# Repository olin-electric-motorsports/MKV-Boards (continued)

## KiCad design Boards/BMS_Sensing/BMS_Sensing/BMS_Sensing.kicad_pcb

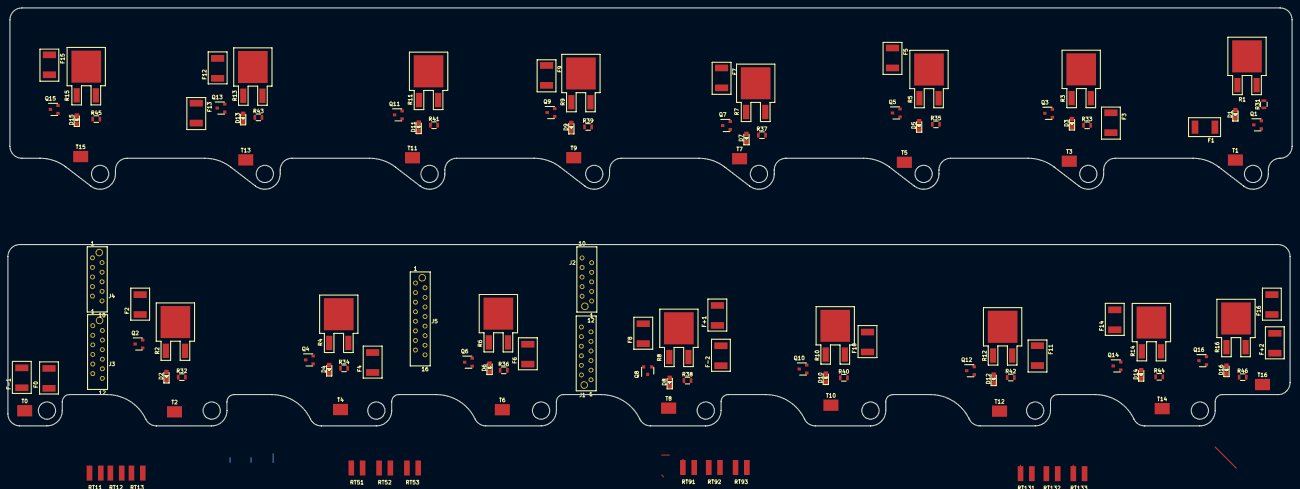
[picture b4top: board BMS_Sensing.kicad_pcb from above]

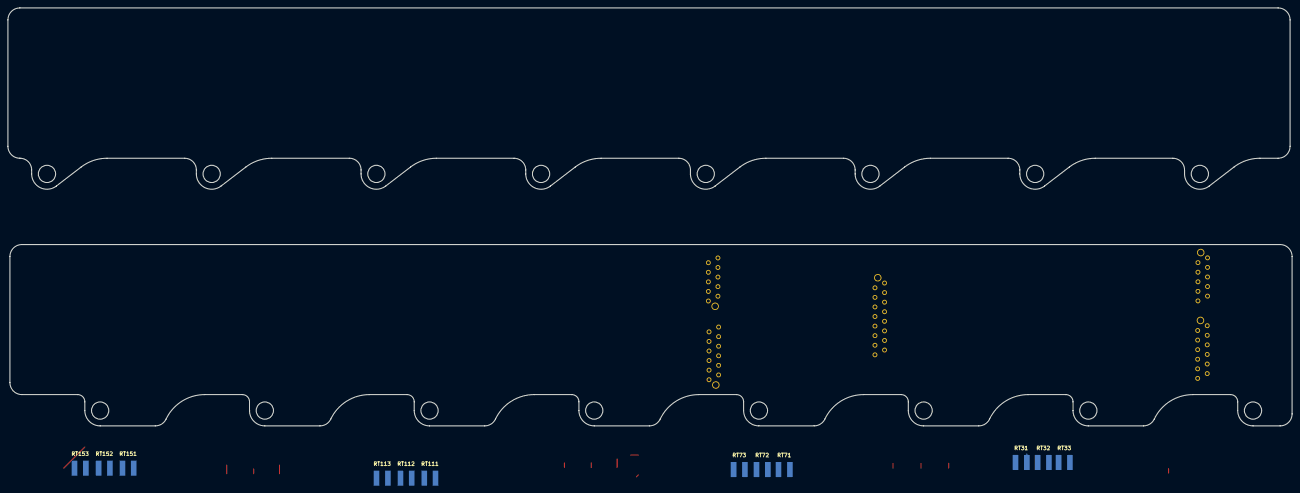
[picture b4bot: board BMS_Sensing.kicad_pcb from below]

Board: 2 copper layers, 340.6 x 110.9 mm, 131 parts (12 on the bottom side), 110 nets.

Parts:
D1, D2, D3, D4, D5, D6, D7, D8, D9, D10, D11, D12, D13, D14, D15, D16: LED_0805; LED_0805_OEM
F0, F1, F2, F3, F4, F5, F6, F7, F8, F9, F10, F11, F12, F13, F14, F15, F16: 200mA_Fuse; Fuse_1812
F+1, F+2: 200mA_Fuse; Fuse_1812
F-1, F-2: 200mA_Fuse; Fuse_1812
J1: MM_M_VT_10; micromatch_female_vert_12
J2, J4: MM_M_VT_12; micromatch_female_vert_10
J3: MM_M_VT_12; micromatch_female_vert_12
J5: MM_M_VT_16; micromatch_female_vert_16
Q1, Q2, Q3, Q4, Q5, Q6, Q7, Q8, Q9, Q10, Q11, Q12, Q13, Q14, Q15, Q16: BSS308PE; SOT-23-3_OEM
R1, R2, R3, R4, R5, R6, R7, R8, R9, R10, R11, R12, R13, R14, R15, R16: R_3.3_25W_TO163; PWR163
R31, R32, R33, R34, R35, R36, R37, R38, R39, R40, R41, R42, R43, R44, R45, R46: R_475; R_0805_OEM
RT11, RT12, RT13, RT31, RT32, RT33, RT51, RT52, RT53, RT71, RT72, RT73, RT91, RT92, RT93, RT111, RT112, RT113, RT131, RT132, RT133, RT151, RT152, RT153: Thermistor
T0, T1, T2, T3, T4, T5, T6, T7, T8, T9, T10, T11, T12, T13, T14, T15, T16: Tab_connect_BMS

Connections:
/C0: F0.2, J1.9
/C1: F1.2, J1.8
/C1_T1: J1.7, RT11.1
/C1_T2: J1.6, RT12.1
/C1_T3: J1.5, RT13.1
/C2: F2.2, J2.11
/C3: F3.2, J1.4
/C3_T1: J2.9, RT31.1
/C3_T2: J2.8, RT32.1
/C3_T3: J2.7, RT33.1
/C4: F4.2, J2.10
/C5: F5.2, J1.3
/C5_T1: J1.2, RT51.1
/C5_T2: J1.1, RT52.1
/C5_T3: J3.12, RT53.1
/C6: F6.2, J2.6
/C7: F7.2, J3.11
/C7_T1: J2.2, RT71.1
/C7_T2: J2.1, RT72.1
/C8: F8.2, J2.3
/C9: F9.2, J3.10
/C9_T1: J3.9, RT91.1
/C9_T2: J3.8, RT92.1
/C9_T3: J3.7, RT93.1
/C10: F10.2, J4.11
/C11: F11.2, J3.6
/C11_T1: J4.9, RT111.1
/C11_T2: J4.8, RT112.1
/C11_T3: J4.7, RT113.1
/C12: F12.2, J4.10
/C13: F13.2, J3.5
/C13_T1: J3.4, RT131.1
/C13_T2: J3.3, RT132.1
/C13_T3: J3.2, RT133.1
/C14: F14.2, J4.6
/C15: F15.2, J3.1
/C15_T1: J4.3, RT151.1
/C15_T2: J4.2, RT152.1
/C15_T3: J4.1, RT153.1
/C16: F16.2, J4.4
/GND1: RT11.2, RT12.2, RT13.2, RT31.2, RT32.2, RT33.2, RT51.2, RT52.2, RT53.2, RT71.2, RT72.2, RT73.2, RT91.2, RT92.2, RT93.2, RT111.2, RT112.2, RT113.2, RT131.2, RT132.2, RT133.2, RT151.2, RT152.2, RT153.2
/Q1: J5.16, Q1.1
/Q2: J5.15, Q2.1
/Q3: J5.14, Q3.1
/Q4: J5.13, Q4.1
/Q5: J5.12, Q5.1
/Q6: J5.11, Q6.1
/Q7: J5.10, Q7.1
/Q8: J5.9, Q8.1
/Q9: J5.8, Q9.1
/Q10: J5.7, Q10.1
/Q11: J5.6, Q11.1
/Q12: J5.5, Q12.1
/Q13: J5.4, Q13.1
/Q14: J5.3, Q14.1
/Q15: J5.2, Q15.1
/Q16: J5.1, Q16.1
/V+1: F+1.2, J4.5
/V+2: F+2.2, J2.5
/V-1: F-1.2, J2.4
/V-2: F-2.2, J1.10
unnamed: D1.1, R31.1
unnamed: D1.2, Q1.3, R1.1
unnamed: D2.1, R32.1
unnamed: D2.2, Q2.3, R2.1
unnamed: D3.1, R33.1
unnamed: D3.2, Q3.3, R3.1
unnamed: D4.1, R34.1
unnamed: D4.2, Q4.3, R4.1
unnamed: D5.1, R35.1
unnamed: D5.2, Q5.3, R5.1
unnamed: D6.1, R36.1
unnamed: D6.2, Q6.3, R6.1
unnamed: D7.1, R37.1
unnamed: D7.2, Q7.3, R7.1
unnamed: D8.1, R38.1
unnamed: D8.2, Q8.3, R8.1
unnamed: D9.1, R39.1
unnamed: D9.2, Q9.3, R9.1
unnamed: D10.1, R40.1
unnamed: D10.2, Q10.3, R10.1
unnamed: D11.1, R41.1
unnamed: D11.2, Q11.3, R11.1
unnamed: D12.1, R42.1
unnamed: D12.2, Q12.3, R12.1
unnamed: D13.1, R43.1
unnamed: D13.2, Q13.3, R13.1
unnamed: D14.1, R44.1
unnamed: D14.2, Q14.3, R14.1
unnamed: D15.1, R45.1
unnamed: D15.2, Q15.3, R15.1
unnamed: D16.1, R46.1
unnamed: D16.2, Q16.3, R16.1
unnamed: F1.1, Q1.2, R2.2, R32.2
unnamed: F2.1, Q2.2, R3.2, R33.2
unnamed: F3.1, Q3.2, R4.2, R34.2
unnamed: F4.1, Q4.2, R5.2, R35.2
unnamed: F5.1, Q5.2, R6.2, R36.2
unnamed: F6.1, Q6.2, R7.2, R37.2
unnamed: F7.1, Q7.2, R8.2, R38.2
unnamed: F9.1, Q9.2, R10.2, R40.2
unnamed: F10.1, Q10.2, R11.2, R41.2
unnamed: F11.1, Q11.2, R12.2, R42.2
unnamed: F12.1, Q12.2, R13.2, R43.2
unnamed: F13.1, Q13.2, R14.2, R44.2
unnamed: F14.1, Q14.2, R15.2, R45.2
unnamed: F15.1, Q15.2, R16.2, R46.2
unnamed: F8.1, F+1.1, F-2.1, Q8.2, R9.2, R39.2
unnamed: F16.1, F+2.1, Q16.2
unnamed: F0.1, F-1.1, R1.2, R31.2

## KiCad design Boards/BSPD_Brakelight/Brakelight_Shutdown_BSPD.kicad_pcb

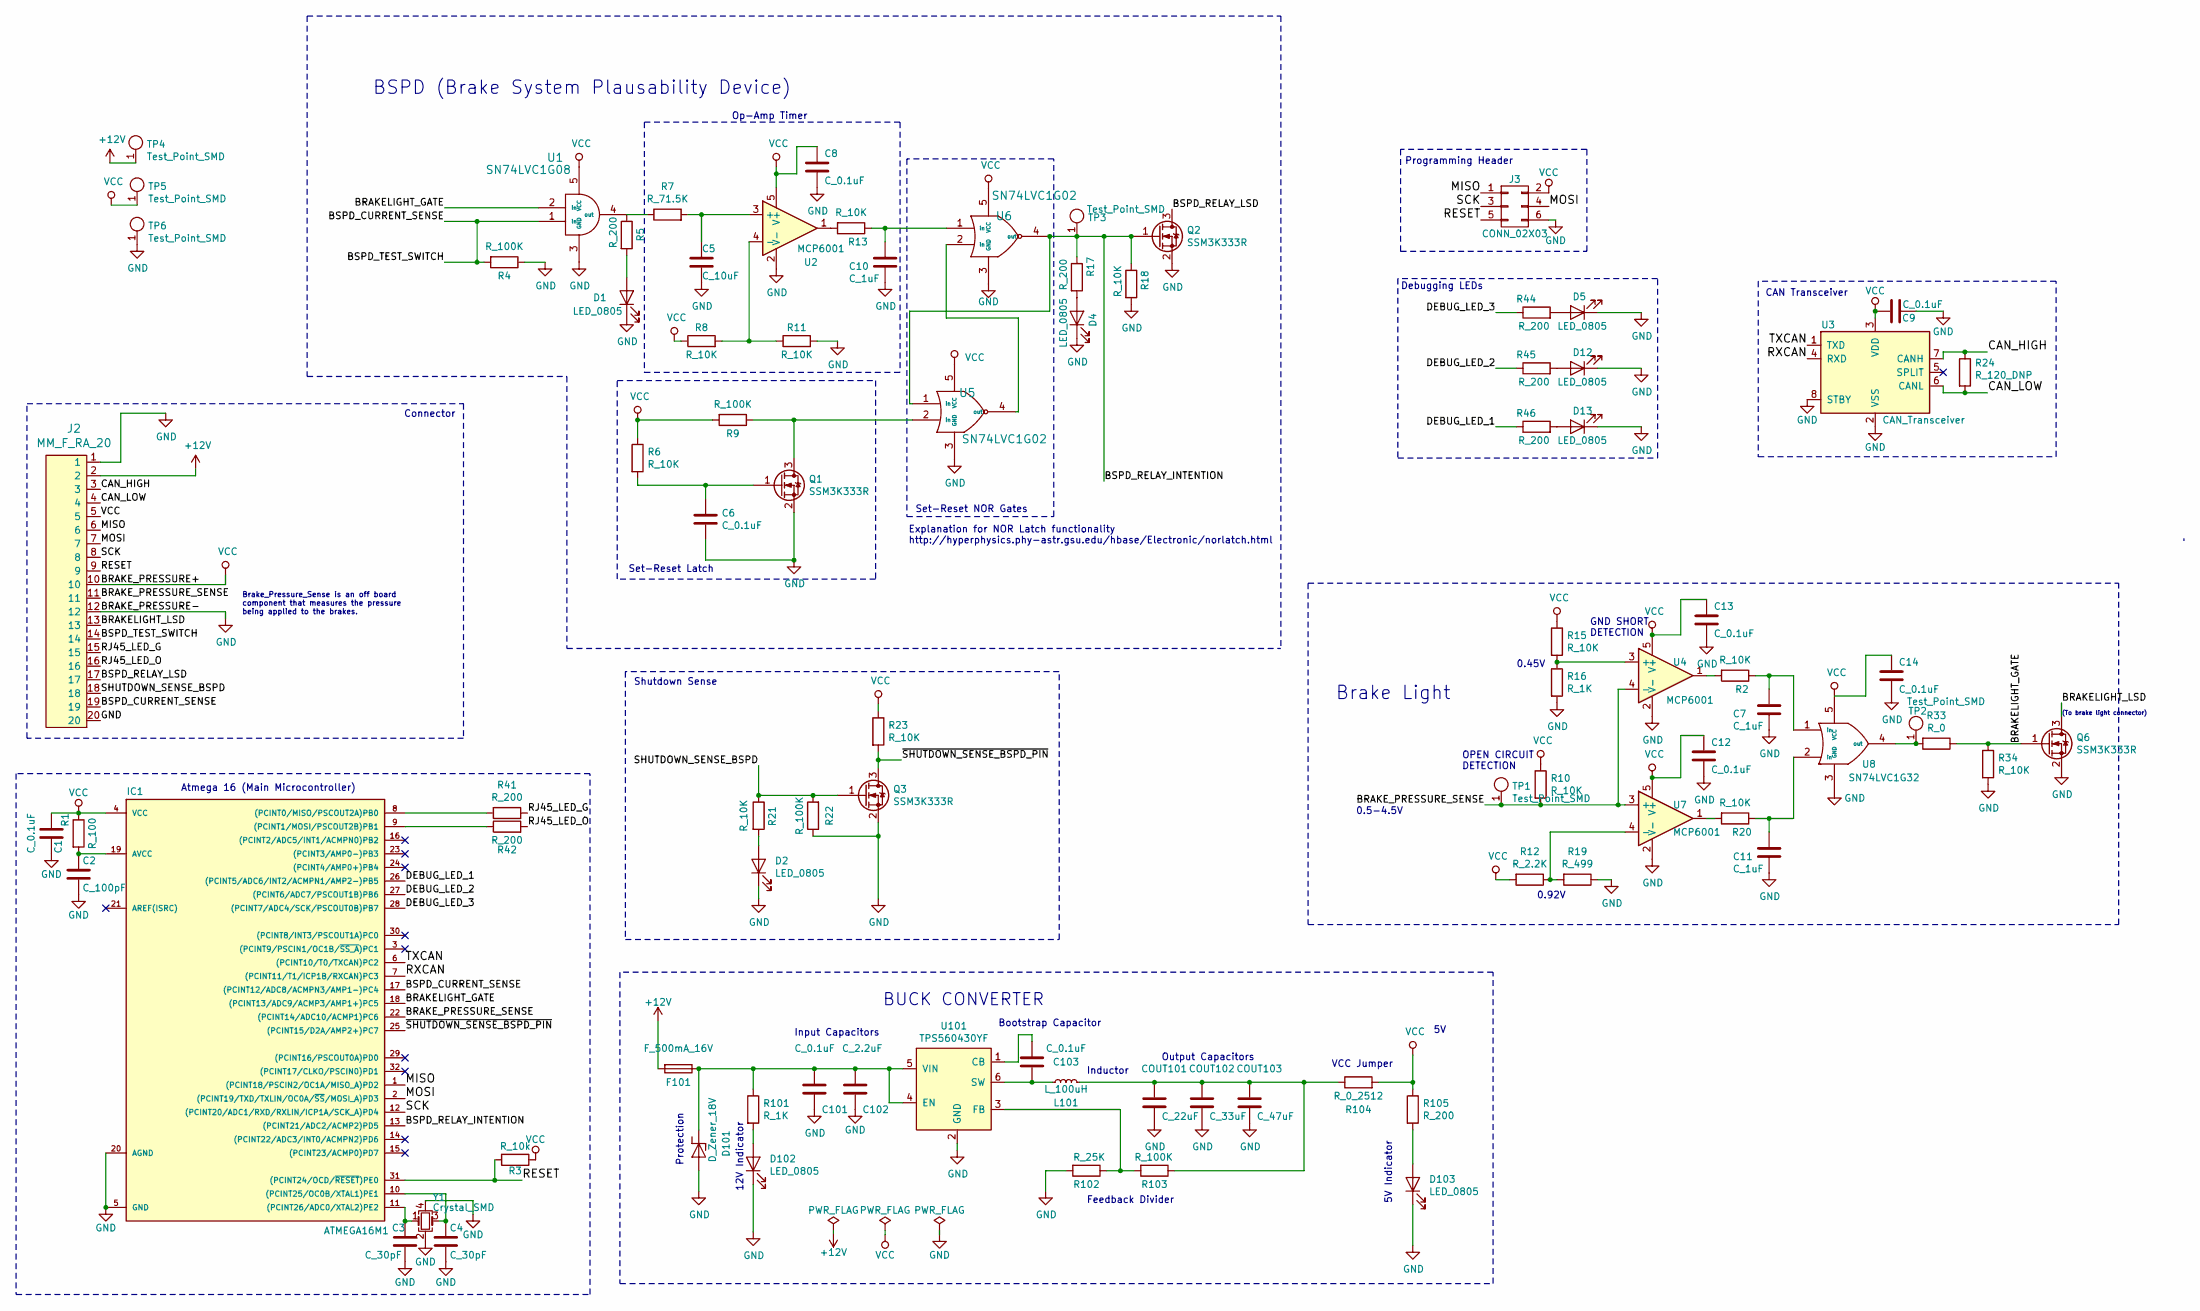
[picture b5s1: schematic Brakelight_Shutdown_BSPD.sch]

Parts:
C1, C6, C8, C9, C12, C13, C14, C101, C103: C_0.1uF; C_0805_OEM; MPN 478-3352-1-ND
C2: C_100pF; C_0805_OEM; MPN 732-7852-1-ND
C3, C4: C_30pF; C_0805_OEM; MPN 1276-1130-1-ND
C5: C_10uF; C_0805_OEM; MPN 1276-1052-1-ND
C7, C10, C11: C_1uF; C_0805_OEM; MPN 1276-2887-1-ND
C102: C_2.2uF; C_0603_1608Metric; MPN 311-1451-1-ND
COUT101: C_22uF; C_1206_OEM; MPN 445-11693-1-ND
COUT102: C_33uF; Fuse_1812; MPN 445-3924-1-ND
COUT103: C_47uF; C_0805_OEM; MPN 1276-6467-1-ND
D1, D2, D4, D5, D12, D13, D102, D103: LED_0805; LED_0805_OEM; MPN 475-1410-1-ND
D101: D_Zener_18V; DO-214AA; MPN SMBJ5355B-TPMSCT-ND
F101: F_500mA_16V; Fuse_1210; MPN 507-1786-1-ND
IC1: ATMEGA16M1; TQFP-32_7x7mm_Pitch0.8mm; MPN ATMEGA16M1-AU-ND
J2: MM_F_RA_20; micromatch_female_ra_20; MPN 2-338070-0
J3: CONN_02X03; Pin_Header_Straight_2x03; MPN 609-3234-ND
L101: L_100uH; L_100uH_OEM; MPN 445-15759-1-ND
Q1, Q2, Q3, Q6: SSM3K333R; SOT-23F; MPN SSM3K333RLFCT-ND
R1: R_100; R_0805_OEM; MPN RNCP0805FTD100RCT-ND
R2, R6, R8, R10, R11, R13, R15, R18, R20, R21, R23, R34: R_10K; R_0805_OEM; MPN CRS0805-FX-1002ELFCT-ND
R3: R_10k; R_0805_OEM; MPN CRS0805-FX-1002ELFCT-ND
R4, R9, R22, R103: R_100K; R_0805_OEM; MPN P100KCCT-ND
R5, R17, R41, R42, R44, R45, R46, R105: R_200; R_0805_OEM; MPN RMCF0805JT200RCT-ND
R7: R_71.5K; R_0805_OEM; MPN P1.07KDACT-ND
R12: R_2.2K; R_0805_OEM; MPN RMCF0805FT2K20CT-ND
R16, R101: R_1K; R_0805_OEM; MPN RNCP0805FTD1K00CT-ND
R19: R_499; R_0805_OEM; MPN P499CCT-ND
R24: R_120_DNP; R_0805_OEM; MPN 667-ERJ-6ENF1200V
R33: R_0; R_0603_1608Metric; MPN P0.0GCT-ND
R102: R_25K; R_0805_OEM; MPN A124124CT-ND; Digi-key Part Number CPF-A-0805B25KE
R104: R_0_2512; R_2512_OEM; MPN A121322CT-ND
TP1, TP2, TP3, TP4, TP5, TP6: Test_Point_SMD
U1: SN74LVC1G08; SOT-23-5_OEM; MPN 296-11601-2-ND
U2, U4, U7: MCP6001; SOT-23-5; MPN MCP6001T-I/OTCT-ND
U3: CAN_Transceiver; SOIC-8_3.9x4.9mm_Pitch1.27mm_OEM; MPN MCP2561-E/SN-ND
U5, U6: SN74LVC1G02; SOT-23-5_OEM; MPN 296-11597-1-ND
U8: SN74LVC1G32; SOT-23-5_OEM; MPN 296-9847-1-ND
U101: TPS560430YF; SOT-23-6_OEM; MPN TPS560430YFDBVR-ND
Y1: Crystal_SMD; Crystal_SMD_FA238; MPN 887-1125-1-ND

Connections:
+12V: F101.2, J2.2, TP4.1
/BRAKELIGHT_GATE: IC1.18 ((PCINT13/ADC9/ACMP3/AMP1+)PC5), Q6.1 (G), R33.1, R34.1, U1.2 (in)
/BRAKELIGHT_LSD: J2.13, Q6.3 (D)
/BRAKE_PRESSURE_SENSE: IC1.22 ((PCINT14/ADC10/ACMP1)PC6), J2.11, R10.2, TP1.1, U4.4 (-), U7.3 (+)
/BSPD_CURRENT_SENSE: IC1.17 ((PCINT12/ADC8/ACMPN3/AMP1-)PC4), J2.14, J2.19, R4.2, U1.1 (in)
/BSPD_RELAY_INTENTION: IC1.13 ((PCINT21/ADC2/ACMP2)PD5), Q2.1 (G), R17.1, R18.1, TP3.1, U5.1 (in), U6.4 (out)
/BSPD_RELAY_LSD: J2.17, Q2.3 (D)
/CAN_HIGH: J2.3, R24.1, U3.7 (CANH)
/CAN_LOW: J2.4, R24.2, U3.6 (CANL)
/DEBUG_LED_1: IC1.26 ((PCINT5/ADC6/INT2/ACMPN1/AMP2-)PB5), R46.1
/DEBUG_LED_2: IC1.27 ((PCINT6/ADC7/PSCOUT1B)PB6), R45.1
/DEBUG_LED_3: IC1.28 ((PCINT7/ADC4/SCK/PSCOUT0B)PB7), R44.1
/MISO: IC1.1 ((PCINT18/PSCIN2/OC1A/MISO_A)PD2), J2.6, J3.1
/MOSI: IC1.2 ((PCINT19/TXD/TXLIN/OC0A/~SS~/MOSI_A)PD3), J2.7, J3.4
/RESET: IC1.31 ((PCINT24/OCD/~RESET~)PE0), J2.9, J3.5, R3.2
/RJ45_LED_G: J2.15, R41.1
/RJ45_LED_O: J2.16, R42.2
/RXCAN: IC1.7 ((PCINT11/T1/ICP1B/RXCAN)PC3), U3.4 (RXD)
/SCK: IC1.12 ((PCINT20/ADC1/RXD/RXLIN/ICP1A/SCK_A)PD4), J2.8, J3.3
/SHUTDOWN_SENSE_BSPD: J2.18, Q3.1 (G), R21.1, R22.2
/TXCAN: IC1.6 ((PCINT10/T0/TXCAN)PC2), U3.1 (TXD)
/~SHUTDOWN_SENSE_BSPD_PIN: IC1.25 ((PCINT15/D2A/AMP2+)PC7), Q3.3 (D), R23.2
GND: C1.2, C2.2, C3.2, C4.2, C5.2, C6.2, C7.2, C8.2, C9.2, C10.2, C11.2, C12.2, C13.2, C14.2, C101.2, C102.2, COUT101.2, COUT102.2, COUT103.2, D1.1 (K), D2.1 (K), D4.1 (K), D5.1 (K), D12.1 (K), D13.1 (K), D101.2 (A), D102.1 (K), D103.1 (K), IC1.5 (GND), IC1.20 (AGND), J2.1, J2.12, J2.20, J3.6, Q1.2 (S), Q2.2 (S), Q3.2 (S), Q6.2 (S), R4.1, R11.2, R16.2, R18.2, R19.1, R22.1, R34.2, R102.2, TP6.1, U1.3 (GND), U2.2 (V-), U3.2 (VSS), U3.8 (STBY), U4.2 (V-), U5.3 (GND), U6.3 (GND), U7.2 (V-), U8.3 (GND), U101.2 (GND), Y1.2, Y1.4
unnamed: C2.1, IC1.19 (AVCC), R1.2
unnamed: C3.1, IC1.11 ((PCINT26/ADC0/XTAL2)PE2), Y1.1
unnamed: C4.1, IC1.10 ((PCINT25/OC0B/XTAL1)PE1), Y1.3
unnamed: C5.1, R7.2, U2.3 (+)
unnamed: C6.1, Q1.1 (G), R6.2
unnamed: C7.1, R2.1, U8.1 (in)
unnamed: C10.1, R13.1, U6.1 (in)
unnamed: C11.1, R20.1, U8.2 (in)
unnamed: C101.1, C102.1, D101.1 (K), F101.1, R101.1, U101.4 (EN), U101.5 (VIN)
unnamed: C103.1, L101.1, U101.6 (SW)
unnamed: C103.2, U101.1 (CB)
unnamed: COUT101.1, COUT102.1, COUT103.1, L101.2, R103.1, R104.1
unnamed: D1.2 (A), R5.2
unnamed: D2.2 (A), R21.2
unnamed: D4.2 (A), R17.2
unnamed: D5.2 (A), R44.2
unnamed: D12.2 (A), R45.2
unnamed: D13.2 (A), R46.2
unnamed: D102.2 (A), R101.2
unnamed: D103.2 (A), R105.2
unnamed: IC1.8 ((PCINT0/MISO/PSCOUT2A)PB0), R41.2
unnamed: IC1.9 ((PCINT1/MOSI/PSCOUT2B)PB1), R42.1
unnamed: Q1.3 (D), R9.1, U5.2 (in)
unnamed: R2.2, U4.1
unnamed: R5.1, R7.1, U1.4 (out)
unnamed: R8.2, R11.1, U2.4 (-)
unnamed: R12.1, R19.2, U7.4 (-)
unnamed: R13.2, U2.1
unnamed: R15.2, R16.1, U4.3 (+)
unnamed: R20.2, U7.1
unnamed: R33.2, TP2.1, U8.4 (out)
unnamed: R102.1, R103.2, U101.3 (FB)
unnamed: U5.4 (out), U6.2 (in)
VCC: C1.1, C8.1, C9.1, C12.1, C13.1, C14.1, IC1.4 (VCC), J2.5, J2.10, J3.2, R1.1, R3.1, R6.1, R8.1, R9.2, R10.1, R12.2, R15.1, R23.1, R104.2, R105.1, TP5.1, U1.5 (VCC), U2.5 (V+), U3.3 (VDD), U4.5 (V+), U5.5 (VCC), U6.5 (VCC), U7.5 (V+), U8.5 (VCC)

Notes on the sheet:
(To brake light connector)
Atmega 16 (Main Microcontroller)
BSPD (Brake System Plausability Device)
Op-Amp Timer
Set-Reset Latch
Set-Reset NOR Gates
Brake Light
Explanation for NOR Latch functionality http://hyperphysics.phy-astr.gsu.edu/hbase/Electronic/norlatch.html
Input Capacitors
12V Indicator
Protection
BUCK CONVERTER
Feedback Divider
Inductor
Bootstrap Capacitor
Output Capacitors
VCC Jumper
5V Indicator
0.92V
0.45V
0.5-4.5V
OPEN CIRCUIT DETECTION
GND SHORT DETECTION
Brake_Pressure_Sense is an off board component that measures the pressure being applied to the brakes.
CAN Transceiver
Programming Header
Debugging LEDs
Connector
Shutdown Sense

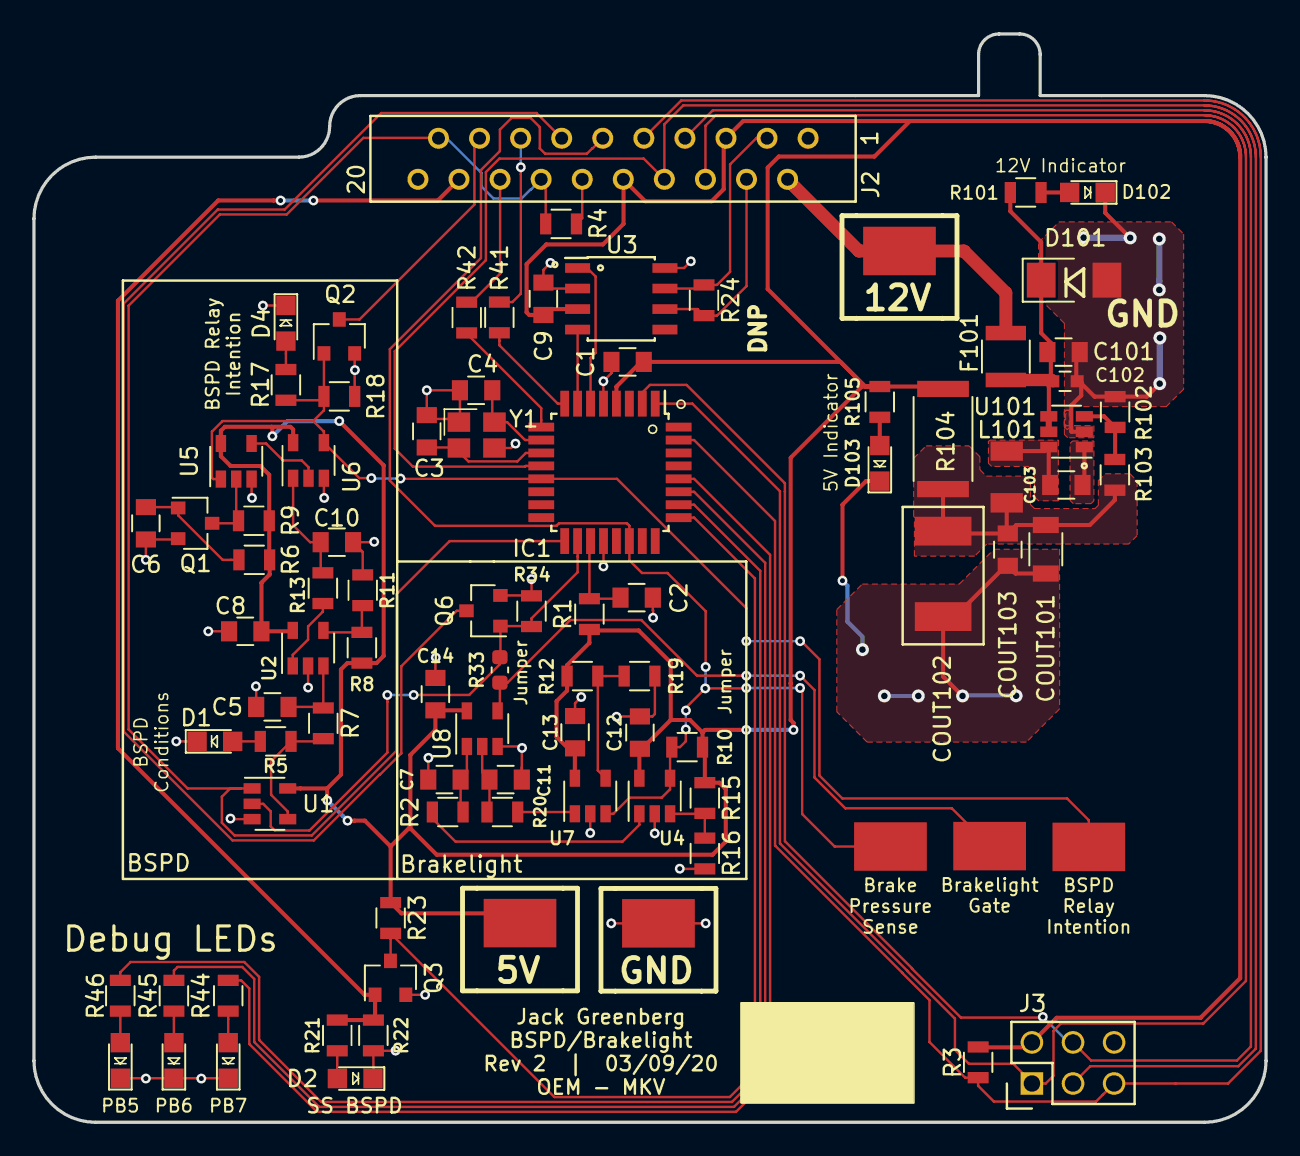
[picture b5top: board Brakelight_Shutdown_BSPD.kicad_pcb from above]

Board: 2 copper layers, 76.2 x 67.3 mm, 89 parts (0 on the bottom side), 57 nets.

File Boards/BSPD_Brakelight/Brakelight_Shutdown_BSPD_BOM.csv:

Reference, Quantity, Value, Footprint, Datasheet, MFN, MPN, Package, PurchasingLink, Digi-key Part Number, Link, Purchasing Link
C10 C7 C11 ,3,"C_1uF","footprints:C_0805_OEM","http://www.samsungsem.com/kr/support/product-search/mlcc/__i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","DK","1276-2887-1-ND","","https://www.digikey.com/product-detail/en/samsung-electro-me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","","",""
C102 ,1,"C_2.2uF","Capacitors_SMD:C_0603","http://www.yageo.com/documents/recent/UPY-GPHC_X5R_4V-to-50V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","DK","311-1451-1-ND","","https://www.digikey.com/product-detail/en/yageo/CC0603KRX5R6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","","",""
C2 ,1,"C_100pF","footprints:C_0805_OEM","https://content.kemet.com/datasheets/KEM_C1003_C0G_SMD.pdf","Digi-Key","399-1122-1-ND","Value","https://www.digikey.com/product-detail/en/kemet/C0805C101J5G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","","",""
C4 C3 ,2,"C_30pF","footprints:C_0805_OEM","https://media.digikey.com/pdf/Data%20Sheets/Samsung%20PDFs/C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","Digi-Key","1276-1130-1-ND","Value","https://www.digikey.com/product-detail/en/samsung-electro-me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","","",""
C5 ,1,"C_10uF","footprints:C_0805_OEM","http://www.samsungsem.com/kr/support/product-search/mlcc/__i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","DK","1276-1052-1-ND","","https://www.digikey.com/product-detail/en/samsung-electro-me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","","",""
C9 C8 C6 C1 C101 C103 C13 C12 C14 ,9,"C_0.1uF","footprints:C_0805_OEM","http://datasheets.avx.com/X7RDielectric.pdf","Digi-Key","478-3352-1-ND","Value","https://www.digikey.com/products/en?keywords=478-3352-1-ND","","",""
COUT101 ,1,"C_22uF","footprints:C_1206_OEM","https://product.tdk.com/info/en/catalog/datasheets/mlcc_comm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","DK","445-11693-1-ND","","https://www.digikey.com/product-detail/en/tdk-corporation/C3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","","",""
COUT102 ,1,"C_33uF","footprints:Fuse_1812","https://product.tdk.com/info/en/catalog/datasheets/mlcc_comm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","C4532X7R1C336M250KC","445-3924-1-ND","","https://www.digikey.com/product-detail/en/tdk-corporation/C4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","","",""
COUT103 ,1,"C_47uF","footprints:C_0805_OEM","http://www.samsungsem.com/kr/support/product-search/mlcc/__i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","DK","1276-6467-1-ND","","https://www.digikey.com/product-detail/en/samsung-electro-me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","","",""
D1 D4 D5 D12 D13 D103 D102 D2 ,8,"LED_0805","footprints:LED_0805_OEM","http://www.osram-os.com/Graphics/XPic9/00078860_0.pdf","DK","475-1410-1-ND","","https://www.digikey.com/products/en?keywords=475-1410-1-ND","","",""
D101 ,1,"D_Zener_18V","footprints:DO-214AA","http://www.mccsemi.com/up_pdf/SMBJ5338B-SMBJ5388B(SMB).pdf","DK","SMBJ5355B-TPMSCT-ND","","https://www.digikey.com/products/en?keywords=SMBJ5355B-TPMSCT-ND","","",""
F101 ,1,"F_500mA_16V","footprints:Fuse_1210","https://belfuse.com/resources/CircuitProtection/datasheets/0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","DK","507-1786-1-ND","","https://www.digikey.com/product-detail/en/bel-fuse-inc/0ZCH0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","","",""
IC1 ,1,"ATMEGA16M1","footprints:TQFP-32_7x7mm_Pitch0.8mm","http://www.atmel.com/Images/Atmel-8209-8-bit%20AVR%20ATmega1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","Digi-Key","ATMEGA16M1-AU-ND","Value","https://www.digikey.com/product-detail/en/atmel/ATMEGA16M1-A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","","",""
J2 ,1,"MM_F_RA_20","footprints:micromatch_female_ra_20","http://www.te.com/commerce/DocumentDelivery/DDEController?Ac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","TE","2-338070-0","","http://www.te.com/usa-en/product-2-338070-0.html","","",""
J3 ,1,"CONN_02X03","footprints:Pin_Header_Straight_2x03","http://portal.fciconnect.com/Comergent//fci/drawing/67996.pdf","Digi-Key","609-3234-ND","Value","https://www.digikey.com/product-detail/en/amphenol-fci/67997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","","",""
L101 ,1,"L_100uH","footprints:L_100uH","https://product.tdk.com/info/en/catalog/datasheets/inductor_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","Digikey","445-15759-1-ND","","","","https://www.digikey.com/product-detail/en/tdk-corporation/NL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",""
Q1 Q2 Q6 Q3 ,4,"SSM3K333R","footprints:SOT-23F","https://drive.google.com/drive/folders/0B-V-iZf33Y4GNzhDQTJZanJRbVk","DK","SSM3K333RLFCT-ND","","https://www.digikey.com/product-detail/en/toshiba-semiconduc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","","",""
R1 ,1,"R_100","footprints:R_0805_OEM","https://www.seielect.com/Catalog/SEI-rncp.pdf","Digi-Key","RNCP0805FTD100RCT-ND","Value","https://www.digikey.com/products/en?keywords=RNCP0805FTD100RCT-ND","","",""
R102 ,1,"R_25K","footprints:R_0805_OEM","https://www.te.com/commerce/DocumentDelivery/DDEController?A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","A124124CT-ND","","","https://www.digikey.com/product-detail/en/te-connectivity-pa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","CPF-A-0805B25KE","",""
R104 ,1,"R_0_2512","footprints:R_2512_OEM","http://www.te.com/commerce/DocumentDelivery/DDEController?Ac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","DK","A121322CT-ND","","https://www.digikey.com/products/en?keywords=A121322CT-ND","","",""
R12 ,1,"R_2.2K","footprints:R_0805_OEM","https://www.seielect.com/Catalog/SEI-RMCF_RMCP.pdf","DK","RMCF0805FT2K20CT-ND","","https://www.digikey.com/product-detail/en/stackpole-electron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","","",""
R14 R33 ,2,"R_0","footprints:R_0603_1608Metric","http://industrial.panasonic.com/www-cgi/jvcr13pz.cgi?E+PZ+3+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","DK","P0.0GCT-ND","","https://www.digikey.com/product-detail/en/panasonic-electron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","","",""
R16 R101 ,2,"R_1K","footprints:R_0805_OEM","https://www.seielect.com/Catalog/SEI-rncp.pdf","DK","RNCP0805FTD1K00CT-ND","","https://www.digikey.com/products/en?keywords=RNCP0805FTD1K00CT-ND","","",""
R19 ,1,"R_499","footprints:R_0805_OEM","https://industrial.panasonic.com/cdbs/www-data/pdf/RDA0000/A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","DK","P499CCT-ND","","https://www.digikey.com/product-detail/en/panasonic-electron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","","",""
R24 ,1,"R_120_DNP","footprints:R_0805_OEM","https://www.mouser.com/datasheet/2/315/AOA0000C304-1149620.pdf","DK","667-ERJ-6ENF1200V","","https://www.mouser.com/ProductDetail/Panasonic-Industrial-De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","","",""
R3 ,1,"R_10k","footprints:R_0805_OEM","http://www.bourns.com/data/global/pdfs/CRS.pdf","Digi-Key","CRS0805-FX-1002ELFCT-ND","Value","https://www.digikey.com/products/en?keywords=CRS0805-FX-1002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","","",""
R4 R9 R103 R22 ,4,"R_100K","footprints:R_0805_OEM","https://industrial.panasonic.com/cdbs/www-data/pdf/RDA0000/A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","DK","P100KCCT-ND","","https://www.digikey.com/product-detail/en/panasonic-electron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","","",""
R5 R17 R41 R42 R44 R45 R46 R105 ,8,"R_200","footprints:R_0805_OEM","https://www.seielect.com/Catalog/SEI-RMCF_RMCP.pdf","DK","RMCF0805JT200RCT-ND","","https://www.digikey.com/products/en?keywords=RMCF0805JT200RCT-ND","","",""
R7 ,1,"R_71.5K","footprints:R_0805_OEM","","DK","P1.07KDACT-ND","","","","",""
R8 R11 R13 R6 R18 R34 R15 R10 R2 R20 R23 R21 ,12,"R_10K","footprints:R_0805_OEM","http://www.bourns.com/data/global/pdfs/CRS.pdf","DK","CRS0805-FX-1002ELFCT-ND","","https://www.digikey.com/products/en?keywords=CRS0805-FX-1002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","","",""
U1 ,1,"SN74LVC1G08","footprints:SOT-23-5_OEM","http://www.ti.com/lit/ds/symlink/sn74lvc1g08.pdf","DK","296-11602-1-ND","","https://www.digikey.com/product-detail/en/texas-instruments/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","","",""
U101 ,1,"TPS560430YF","footprints:SOT-23-6_OEM","http://www.ti.com/lit/ds/symlink/tps560430.pdf","TPS560430YFDBVR-ND","TPS560430YFDBVR","","","","","https://www.digikey.com/product-detail/en/texas-instruments/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"
U2 U7 U4 ,3,"MCP6001","footprints:SOT-23-5_OEM","http://ww1.microchip.com/downloads/en/DeviceDoc/21733j.pdf","DK","MCP6001T-I/OTCT-ND","","https://www.digikey.com/product-detail/en/microchip-technolo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","","",""
U3 ,1,"CAN_Transceiver","footprints:SOIC-8_3.9x4.9mm_Pitch1.27mm_OEM","http://www.microchip.com/mymicrochip/filehandler.aspx?ddocna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","Digi-Key","MCP2561-E/SN-ND","Value","https://www.digikey.com/products/en?keywords=mcp2561-e%2Fsn","","",""
U5 U6 ,2,"SN74LVC1G02","footprints:SOT-23-5_OEM","http://www.ti.com/lit/ds/symlink/sn74lvc1g02.pdf","DK","296-11598-1-ND","","https://www.digikey.com/product-detail/en/texas-instruments/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","","",""
U8 ,1,"SN74LVC1G32","footprints:SOT-23-5_OEM","http://www.ti.com/lit/ds/symlink/sn74lvc1g32.pdf","DK","SN74LVC1G32DBVR","","https://www.digikey.com/product-detail/en/texas-instruments/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","","",""
Y1 ,1,"Crystal_SMD","footprints:Crystal_SMD_FA238","https://support.epson.biz/td/api/doc_check.php?dl=brief_FA-2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","Digi-Key","SER3686CT-ND","Value","https://www.digikey.com/products/en?keywords=SER3686CT-ND","","",""
